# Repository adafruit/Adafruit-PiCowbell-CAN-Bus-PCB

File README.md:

## Adafruit PiCowbell CAN Bus for Pico - MCP2515 CAN Controller PCB

<a href="http://www.adafruit.com/products/5728"><br/>
Click here to purchase one from the Adafruit shop</a>

PCB files for the Adafruit PiCowbell CAN Bus for Pico - MCP2515 CAN Controller. 

Format is EagleCAD schematic and board layout
* https://www.adafruit.com/product/5728

### Description

Ding dong! Hear that? It's the PiCowbell ringing, letting you know that the new Adafruit PiCowbell CAN Bus is in stock and ready to assist your Raspberry Pi Pico and Pico W project connect to CAN bus networks for automotive or robotics projects.

CAN Bus is a small-scale networking standard, originally designed for cars and, yes, busses, but is now used for many robotics or sensor networks that need better range and addressing than I2C and don't have the pins or computational ability to talk on Ethernet. CAN is 2 wire differential, which means it's good for long distances and noisy environments.

Messages are sent at about 1Mbps rate - you set the frequency for the bus and then all 'joiners' must match it, and have an address before the packet so that each node can listen in to messages just for it. New nodes can be attached easily because they just need to connect to the two data lines anywhere in the shared net. Each CAN device sends messages whenever it wants, and thanks to some clever data encoding, can detect if there's a message collision and retransmit later. 

If you'd like to connect your Raspberry Pi Pico to a CAN Bus, the Adafruit PiCowbell CAN Bus has a MCP2515 controller and TJA1051/3 transceiver! The controller used is the MCP2515, an extremely popular and well-supported chipset that has drivers in Arduino and CircuitPython and only requires an SPI port and two pins for chip-select and IRQ. Use it to send and receive messages in either standard or extended format at up to 1 Mbps.

We've added a few nice extras to this PiCowBell to make it useful in many common CAN scenarios:

5V charge-pump voltage generator, so even though you are running 3.3V on a Pico board, it will generate a nice clean 5V as required by the transceiver.
3.5mm terminal block pre-soldered in to get quick access to the High and Low data lines as well as a ground pin.
120-ohm termination resistor on board, you can remove the termination easily by cutting the jumper marked Term on the top of the board.
Pre-connected CS and INT pins on Pico GPIO #20 and #21. You can cut the bottom solder jumpers and use the breakout pads to connect to any two IO pins you like
Each order comes with an assembled PCB and header. You will need to solder in the header yourself, but it's a quick task.

Please Note! There are a lot of possible configurations, and we stock various headers depending on how you want to solder and attach. Especially if you want the Pico on top so that the BOOTSEL button and LED are accessible.

1. Use the Pico Stacking Headers if you want to be able to plug into a breadboard or other accessory with sockets.
2. Use the Pico Socket Headers if you want to plug directly in and have a nice solid connection that doesn't have any poking-out-bits.
3. Use the Short Socket Headers for a very slim but pluggable design; note that you'll want to trim down the Pico's headers or use the short plug headers on the Pico to have a skinny sandwich.
4. Solder the PCB directly to the Pico headers - of course, this is very compact and inexpensive, but you won't be able to remove the PiCowbell.

The PiCowbell CAN Bus provides you with:

* Right angle JST SH connector for I2C / Stemma QT / Qwiic connection. Provides 3V, GND, IO4 (SDA), and IO5 (SCL)
* Reset button - Press to restart your program
* Every pad on the 'bell has a duplicate hole pad next to them for solder-jumpering
* The ground pads have white silkscreen rectangles to easily identify, plus one long ground strip near the reset button
* Gold-plated pads for easy soldering

If using the Philhower Arduino core, the Wire peripheral is already set up to use IO4 and IO5, and SPI is default on IO16, IO18 and IO19. If using CircuitPython or MicroPython, you'll need to let the code know to look at 4+5 for SDA+SCL pins, and configure the SPI port for SCK=18, MOSI=19 and MISO=16.

### License

Adafruit invests time and resources providing this open source design, please support Adafruit and open-source hardware by purchasing products from [Adafruit](https://www.adafruit.com)!

Designed by Limor Fried/Ladyada for Adafruit Industries.

Creative Commons Attribution/Share-Alike, all text above must be included in any redistribution. 
See license.txt for additional details.

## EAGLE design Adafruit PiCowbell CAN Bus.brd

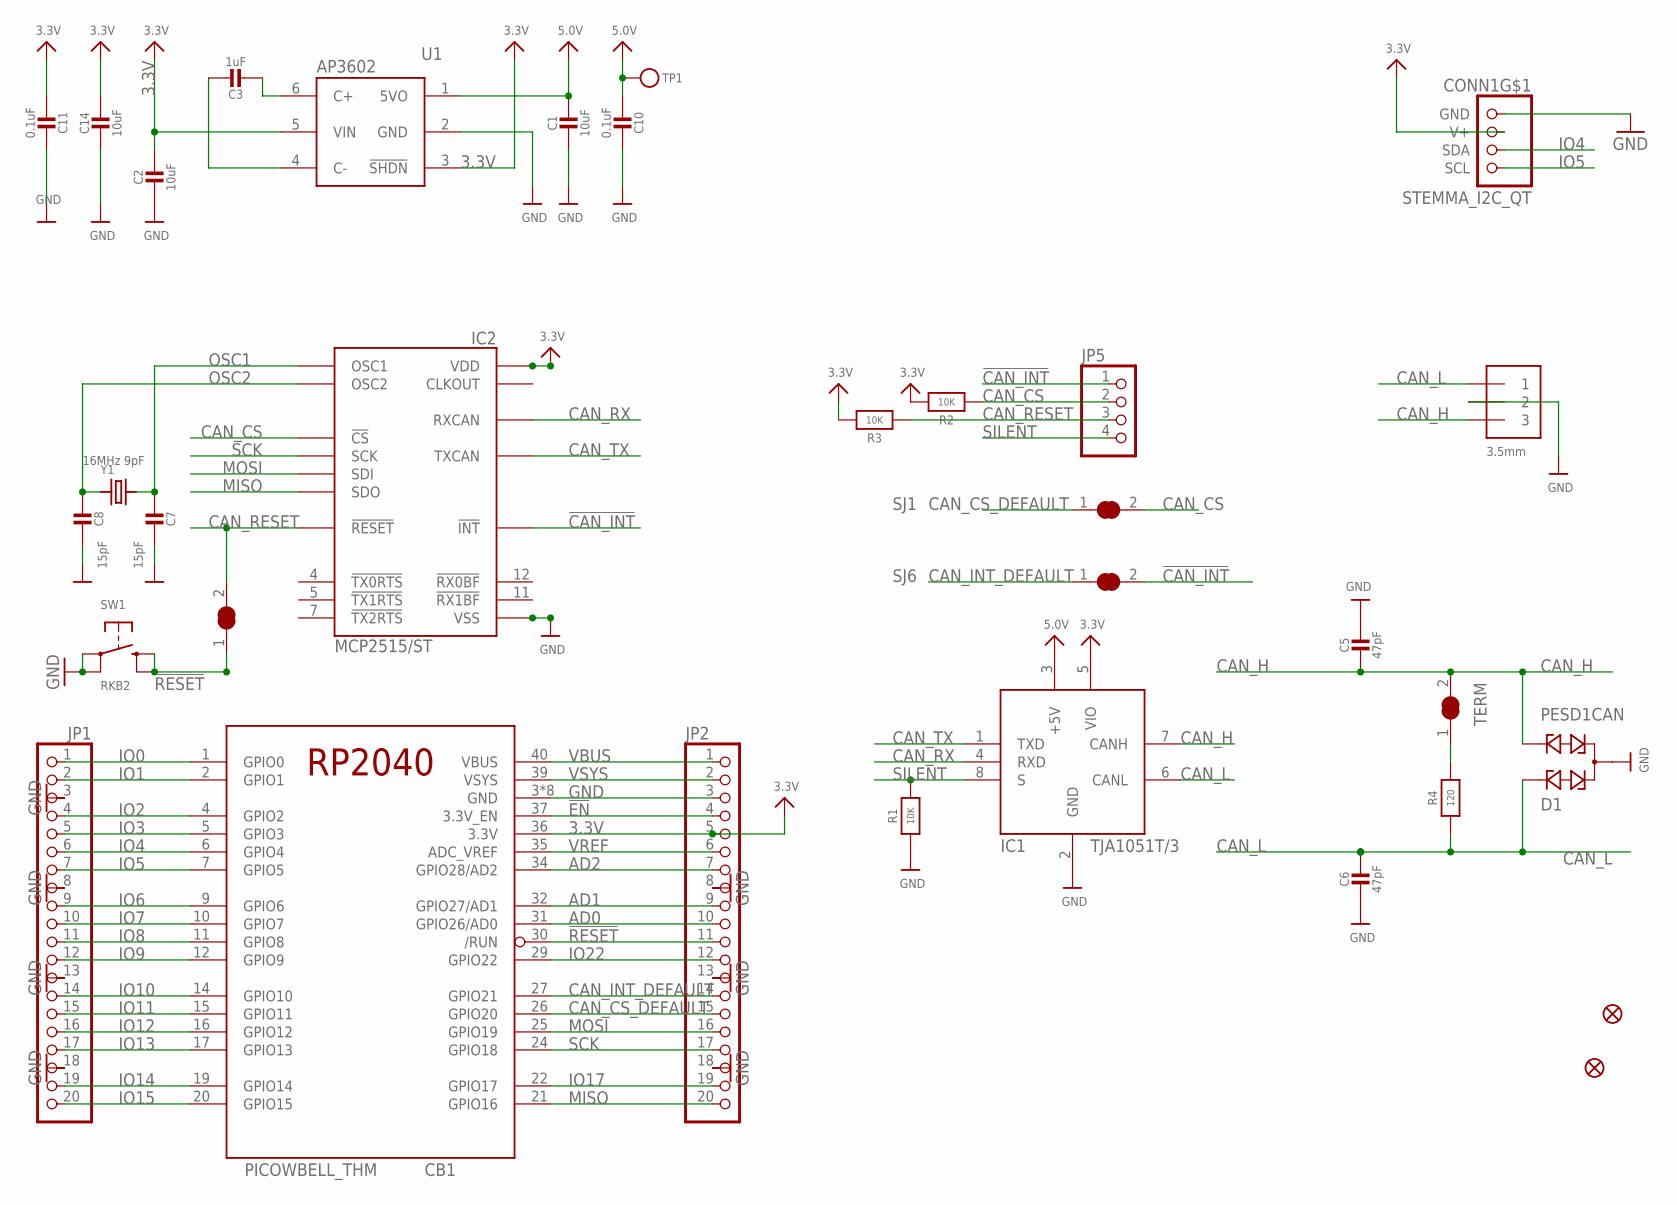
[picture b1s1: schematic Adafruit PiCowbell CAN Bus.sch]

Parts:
C1, C2, C14: 10uF; 0805-NO
C3: 1uF; 0805-NO
C5, C6: 47pF; 0603-NO
C7, C8: 15pF; 0603-NO
C10, C11: 0.1uF; 0603-NO
CAN: 3.5mm; TERMBLOCK_1X3-3.5MM
CB1: PICOWBELL_THM
CONN1: STEMMA_I2C_QT; JST_SH4
D1: PESD1CAN; SOT23
FID1, FID2: FIDUCIAL_1MM
IC1: TJA1051T/3; SOIC8_150MIL
IC2: MCP2515/ST; SSOP20
JP1, JP2: HEADER-1X20_70MIL; 1X20_ROUND_70MIL
JP5: HEADER-1X4ROUND; 1X04_ROUND
R1, R2, R3: 10K; 0603-NO
R4: 120; 0603-NO
SJ1, SJ5, SJ6: SOLDERJUMPER_CLOSED; SOLDERJUMPER_CLOSEDWIRE
SW1: RKB2; BTN_RKB2_4.6X2.8
TERM: SOLDERJUMPER_CLOSED; SOLDERJUMPER_CLOSEDWIRE
TP1: TESTPOINTROUND1.5MM; TESTPOINT_ROUND_1.5MM
U1: AP3602; SOT23-6
Y1: 16MHz 9pF; CRYSTAL_3.2X2.5

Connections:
3.3V: C2.1, C11.2, C14.1, CB1.36 (3.3V), CONN1.2 (V+), IC1.5 (VIO), IC2.20 (VDD), JP2.5, R2.2, R3.2, U1.3 (!SHDN), U1.5 (VIN)
5.0V: C1.1, C10.2, IC1.3 (+5V), TP1.P$1, U1.1 (5VO)
!CAN_INT: IC2.13 (!INT), JP5.1, SJ6.2
!EN: CB1.37 (3.3V_EN), JP2.4
!RESET: CB1.30 (/RUN), JP2.11, SJ5.1, SW1.B (S), SW1.B' (S1)
AD0: CB1.31 (GPIO26/AD0), JP2.10
AD1: CB1.32 (GPIO27/AD1), JP2.9
AD2: CB1.34 (GPIO28/AD2), JP2.7
CAN_CS: IC2.18 (!CS), JP5.2, R2.1, SJ1.2
CAN_CS_DEFAULT: CB1.26 (GPIO20), JP2.15, SJ1.1
CAN_H: C5.2, CAN.3, D1.2, IC1.7 (CANH), TERM.2
CAN_INT_DEFAULT: CB1.27 (GPIO21), JP2.14, SJ6.1
CAN_L: C6.1, CAN.1, D1.1, IC1.6 (CANL), R4.1
CAN_RESET: IC2.19 (!RESET), JP5.3, R3.1, SJ5.2
CAN_RX: IC1.4 (RXD), IC2.2 (RXCAN)
CAN_TX: IC1.1 (TXD), IC2.1 (TXCAN)
GND: C1.2, C2.2, C5.1, C6.2, C7.1, C8.1, C10.1, C11.1, C14.2, CAN.2, CB1.3 (GND), CB1.8 (GND), CB1.13 (GND), CB1.18 (GND), CB1.23 (GND), CB1.28 (GND), CB1.33 (GND), CB1.38 (GND), CONN1.1 (GND), D1.3, IC1.2 (GND), IC2.10 (VSS), JP1.3, JP1.8, JP1.13, JP1.18, JP2.3, JP2.8, JP2.13, JP2.18, R1.1, SW1.A, SW1.A' (P1), U1.2 (GND)
IO0: CB1.1 (GPIO0), JP1.1
IO1: CB1.2 (GPIO1), JP1.2
IO2: CB1.4 (GPIO2), JP1.4
IO3: CB1.5 (GPIO3), JP1.5
IO4: CB1.6 (GPIO4), CONN1.3 (SDA), JP1.6
IO5: CB1.7 (GPIO5), CONN1.4 (SCL), JP1.7
IO6: CB1.9 (GPIO6), JP1.9
IO7: CB1.10 (GPIO7), JP1.10
IO8: CB1.11 (GPIO8), JP1.11
IO9: CB1.12 (GPIO9), JP1.12
IO10: CB1.14 (GPIO10), JP1.14
IO11: CB1.15 (GPIO11), JP1.15
IO12: CB1.16 (GPIO12), JP1.16
IO13: CB1.17 (GPIO13), JP1.17
IO14: CB1.19 (GPIO14), JP1.19
IO15: CB1.20 (GPIO15), JP1.20
IO17: CB1.22 (GPIO17), JP2.19
IO22: CB1.29 (GPIO22), JP2.12
MISO: CB1.21 (GPIO16), IC2.17 (SDO), JP2.20
MOSI: CB1.25 (GPIO19), IC2.16 (SDI), JP2.16
unnamed: C3.2, U1.6 (C+)
unnamed: C3.1, U1.4 (C-)
unnamed: R4.2, TERM.1
OSC1: C7.2, IC2.9 (OSC1), Y1.2
OSC2: C8.2, IC2.8 (OSC2), Y1.1
SCK: CB1.24 (GPIO18), IC2.14 (SCK), JP2.17
SILENT: IC1.8 (S), JP5.4, R1.2
VBUS: CB1.40 (VBUS), JP2.1
VREF: CB1.35 (ADC_VREF), JP2.6
VSYS: CB1.39 (VSYS), JP2.2

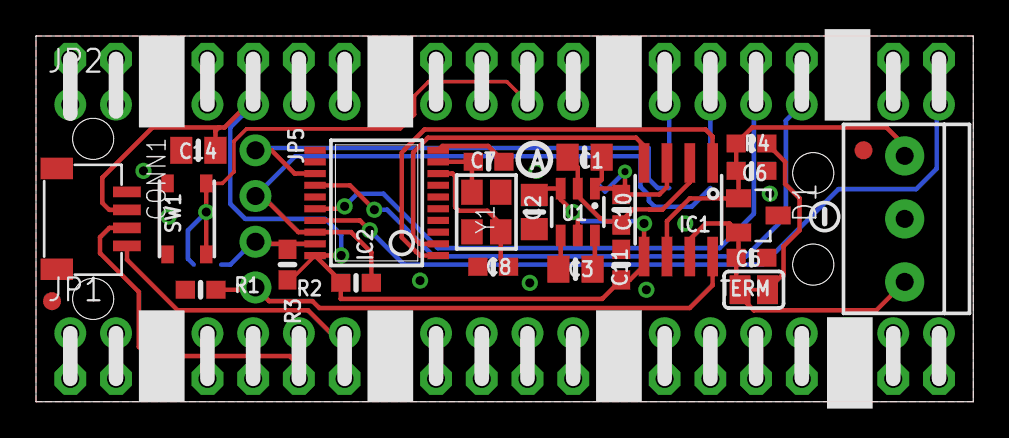
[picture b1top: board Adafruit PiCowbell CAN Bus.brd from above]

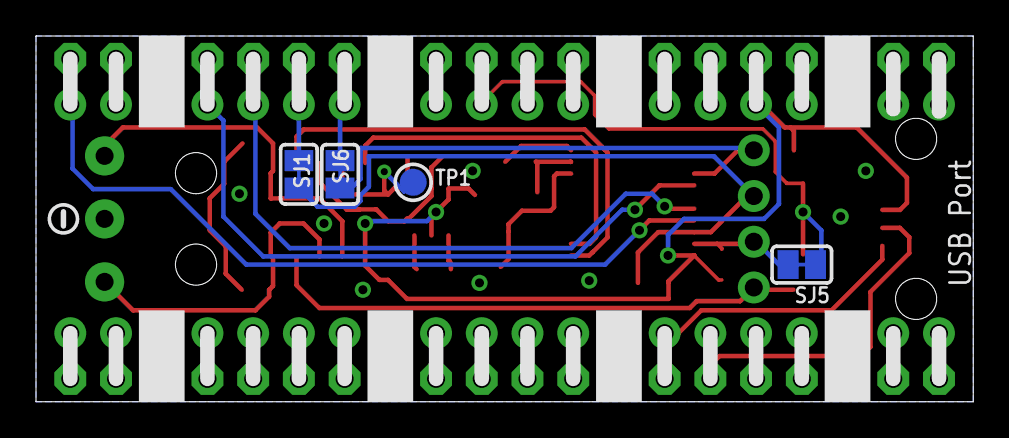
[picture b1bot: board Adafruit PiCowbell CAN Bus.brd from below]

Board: 2 copper layers, 52.1 x 20.3 mm, 84 parts (43 on the bottom side), 47 nets.

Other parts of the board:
PLABEL36: PLABEL36
PLABEL37: PLABEL37
PLABEL38: PLABEL38
PLABEL40: PLABEL40
PLABEL41: PLABEL41
PLABEL42: PLABEL42
PLABEL43: PLABEL43
PLABEL44: PLABEL44
PLABEL45: PLABEL45
PLABEL46: PLABEL46
PLABEL47: PLABEL47
PLABEL49: PLABEL49
PLABEL50: PLABEL50
PLABEL51: PLABEL51
PLABEL52: PLABEL52
PLABEL53: PLABEL53
PLABEL54: PLABEL54
PLABEL55: PLABEL55
PLABEL56: PLABEL56
PLABEL57: PLABEL57
PLABEL58: PLABEL58
PLABEL59: PLABEL59
PLABEL60: PLABEL60
PLABEL61: PLABEL61
PLABEL62: PLABEL62
PLABEL63: PLABEL63
PLABEL64: PLABEL64
PLABEL65: PLABEL65
PLABEL66: PLABEL66
PLABEL67: PLABEL67
PLABEL68: PLABEL68
PLABEL69: PLABEL69
PLABEL70: PLABEL70
PLABEL71: PLABEL71
PLABEL72: PLABEL72
PLABEL73: PLABEL73
PLABEL74: PLABEL74
PLABEL75: PLABEL75
PLABEL76: PLABEL76
PLABEL77: PLABEL77
PLABEL78: PLABEL78
PLABEL79: PLABEL79
PLABEL80: PLABEL80
PLABEL81: PLABEL81
PLABEL82: PLABEL82
PLABEL83: PLABEL83
PLABEL84: PLABEL84
PLABEL85: PLABEL85
U$2, U$34: SYMBOL_MINUS
U$11: PCBFEAT-REV-040

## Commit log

2023-05-03 adding cookiecutter output
2023-05-03 readme spacing

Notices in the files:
parts and their libraries:
microbuilder: This work is placed in the public domain, and may be freely used for commercial and non-commercial work with the following conditions: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
